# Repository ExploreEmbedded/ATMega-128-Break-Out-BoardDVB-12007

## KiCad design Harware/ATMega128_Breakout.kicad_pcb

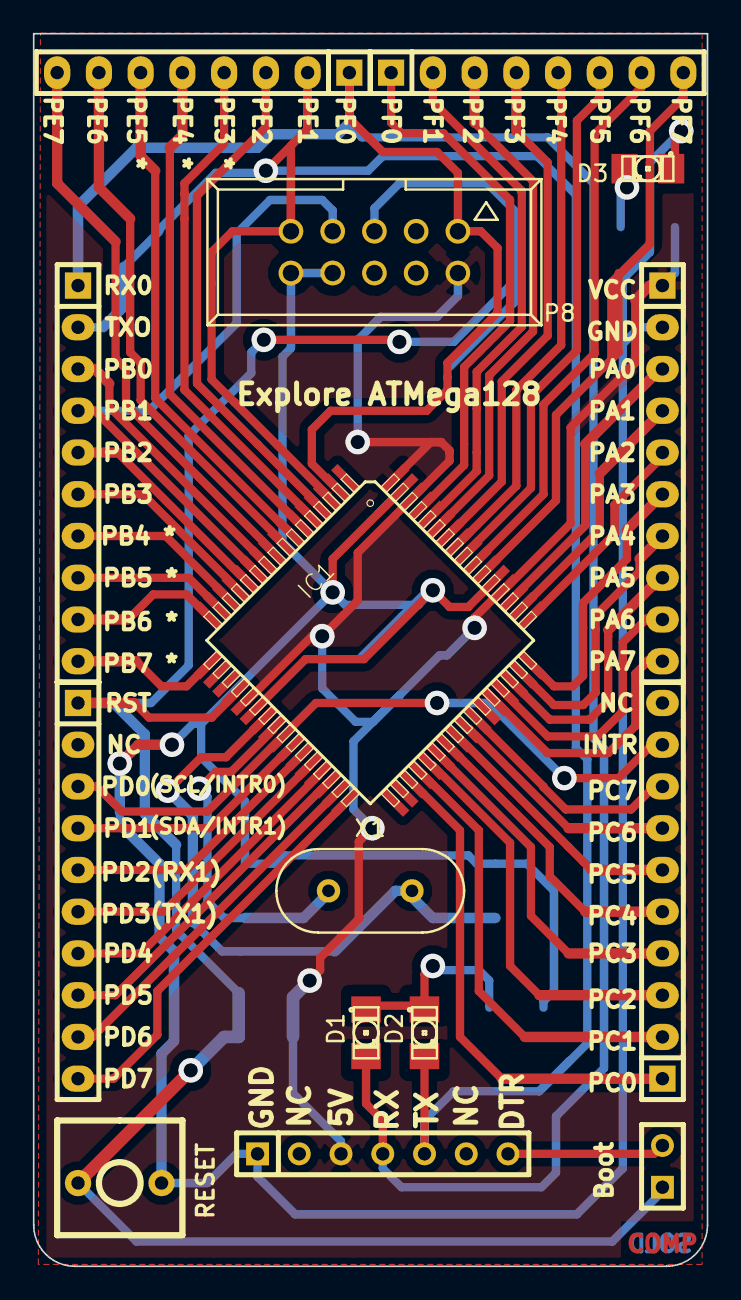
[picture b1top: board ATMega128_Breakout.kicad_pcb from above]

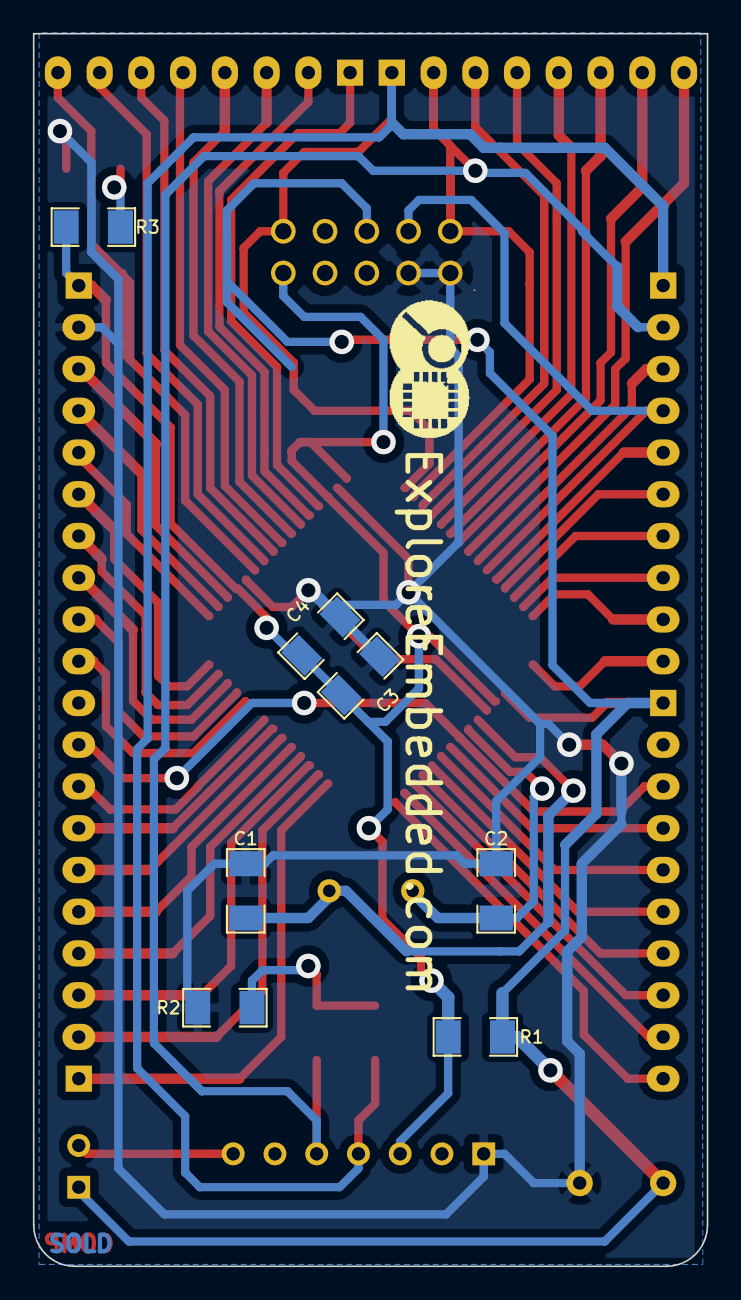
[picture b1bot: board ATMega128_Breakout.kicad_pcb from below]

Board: 2 copper layers, 41.0 x 75.0 mm, 23 parts (8 on the bottom side), 56 nets.

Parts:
C1, C2: 22PF; SM1206
C3, C4: 0.1uF; SM1206
D1, D2, D3: LED; LED-1206_NEW
IC1: ATMEGA128-A; TQFP64_atmega128_XL1
J1, J2: SIL8; SIL-8
JP1: JUMPER; SIL-2
LOGO: LOGO (2)
P1, P2, P3, P4: CONN_10; SIL-10
P6: CONN_7; SIL-7
P8: CONN_5X2; VASCH5x2
R1: 10K; SM1206
R2, R3: 470r; SM1206
SW1: RESET; SW_PUSH_SMALL_2pin_xl
X1: 16Mhz; HC-49V

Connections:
/+5V: C3.1, C4.1, IC1.21, IC1.52, IC1.62, IC1.64, P3.1, P6.3, P8.2, R1.2, R3.1
/INTR: IC1.25, P2.3, P4.9
/RST: IC1.20, JP1.1, P2.1, P8.5, R1.1, SW1.1
/RX0: D1.1, IC1.2, J2.1, P1.1, P6.4, P8.1
/SCK: IC1.11, P1.4, P8.7
/TX0: D2.1, IC1.3, J2.2, P1.2, P6.5, P8.9
GND: C1.1, C2.1, C3.2, C4.2, D3.2, IC1.22, IC1.53, IC1.63, P3.2, P6.1, P8.8, P8.10, R2.2, SW1.2
unnamed: C1.2, IC1.23, X1.2
unnamed: C2.2, IC1.24, X1.1
unnamed: D1.2, D2.2, R2.1
unnamed: D3.1, R3.2
unnamed: IC1.4, J2.3
unnamed: IC1.5, J2.4
unnamed: IC1.6, J2.5
unnamed: IC1.7, J2.6
unnamed: IC1.8, J2.7
unnamed: IC1.9, J2.8
unnamed: IC1.10, P1.3
unnamed: IC1.12, P1.5
unnamed: IC1.13, P1.6
unnamed: IC1.14, P1.7
unnamed: IC1.15, P1.8
unnamed: IC1.16, P1.9
unnamed: IC1.17, P1.10
unnamed: IC1.26, P2.4
unnamed: IC1.27, P2.5
unnamed: IC1.28, P2.6
unnamed: IC1.29, P2.7
unnamed: IC1.30, P2.8
unnamed: IC1.31, P2.9
unnamed: IC1.32, P2.10
unnamed: IC1.35, P4.1
unnamed: IC1.36, P4.2
unnamed: IC1.37, P4.3
unnamed: IC1.38, P4.4
unnamed: IC1.39, P4.5
unnamed: IC1.40, P4.6
unnamed: IC1.41, P4.7
unnamed: IC1.42, P4.8
unnamed: IC1.44, P3.10
unnamed: IC1.45, P3.9
unnamed: IC1.46, P3.8
unnamed: IC1.47, P3.7
unnamed: IC1.48, P3.6
unnamed: IC1.49, P3.5
unnamed: IC1.50, P3.4
unnamed: IC1.51, P3.3
unnamed: IC1.54, J1.8
unnamed: IC1.55, J1.7
unnamed: IC1.56, J1.6
unnamed: IC1.57, J1.5
unnamed: IC1.58, J1.4
unnamed: IC1.59, J1.3
unnamed: IC1.60, J1.2
unnamed: IC1.61, J1.1
unnamed: JP1.2, P6.7

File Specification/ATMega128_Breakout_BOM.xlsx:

Id | Designator | Package | Quantity | Designation | Supplier and ref
1 | IC1 | TQFP64_atmega128_XL1 | 1 | ATMEGA128-A
2 | P8 | VASCH5x2 | 1 | CONN_5X2
3 | SW1 | SW_PUSH_SMALL_2pin_xl | 1 | rst
4 | C2,C1 | SM1206 | 2 | 22PF
5 | R3,R2 | SM1206 | 2 | 470r
6 | D4,D3,D1,D2 | SM1206 | 4 | LED
7 | C4,C3 | SM1206 | 2 | 0.1uF
8 | R1 | SM1206 | 1 | 10K
9 | J2,J1 | SIL-8 | 2 | SIL8
10 | P2,P1,P4,P3 | SIL-10 | 4 | CONN_10
11 | X1 | HC-49V | 1 | 16Mhz
12 | P5 | SIL-2 | 1 | CONN_2

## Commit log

2015-05-22 Added Files
2015-06-02 changed design
2015-07-27 added final files
2015-07-27 final
2015-08-14 Sample code Atmega128
    Sample blink, lcd and UART code
2015-08-15 pdf schematic
2015-08-15 blinky code tested
2015-08-15 updated lib files
    AVR test firmware
2015-08-19 Sample code updated
    RTC,EEPROM,Seven Segment,Keypad,ADC and Switch LED
2015-08-20 UART code added
2016-04-18 Tutorials and code updated
    Tutorials and code updated
